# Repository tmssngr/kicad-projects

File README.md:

- [EEPROM flasher as Arduino shield](EPROM-Shield/README.md)

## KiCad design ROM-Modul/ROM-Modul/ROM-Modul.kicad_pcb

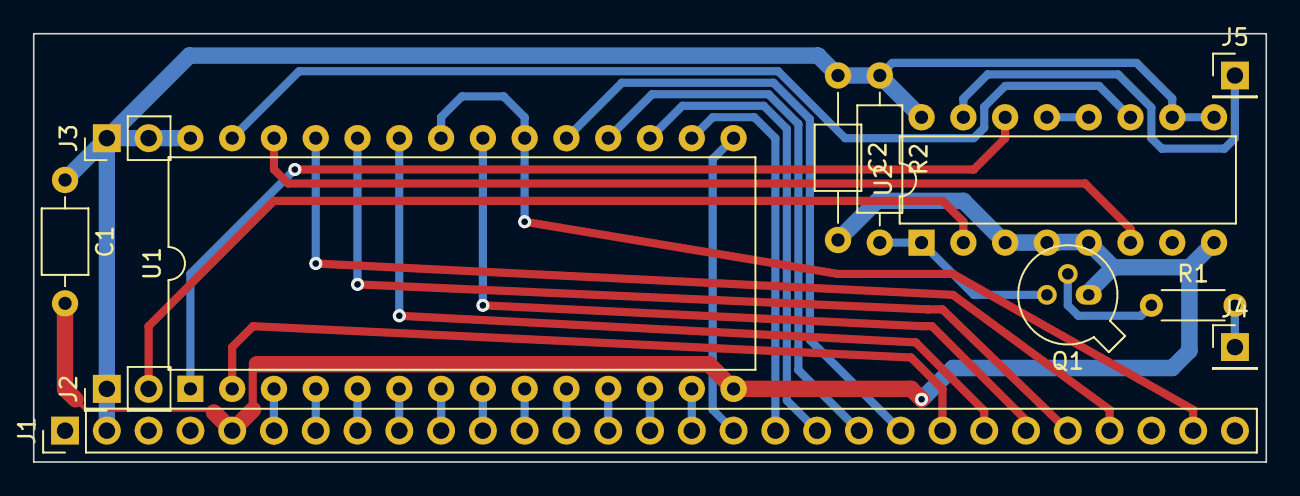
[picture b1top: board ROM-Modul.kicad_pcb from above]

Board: 2 copper layers, 74.9 x 26.0 mm, 12 parts (0 on the bottom side), 32 nets.

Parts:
C1: C; C_Axial_L3.8mm_D2.6mm_P7.50mm_Horizontal
C2: C; C_Axial_L3.8mm_D2.6mm_P10.00mm_Horizontal
J1: Conn_01x29; PinHeader_1x29_P2.54mm_Vertical
J2, J3: Conn_01x02; PinHeader_1x02_P2.54mm_Vertical
J4: /0; PinHeader_1x01_P2.54mm_Vertical
J5: Schritt; PinHeader_1x01_P2.54mm_Vertical
Q1: BC107; TO-18-3
R1: 1k; R_Axial_DIN0204_L3.6mm_D1.6mm_P5.08mm_Horizontal
R2: 10k; R_Axial_DIN0207_L6.3mm_D2.5mm_P10.16mm_Horizontal
U1: 27C512; DIP-28_W15.24mm
U2: 4029; DIP-16_W7.62mm

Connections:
/A0: J1.13, U1.10
/A1: J1.12, U1.9
/A2: J1.11, U1.8
/A3: J1.10, U1.7
/A4: J1.9, U1.6
/A5: J1.8, U1.5
/A6: J1.7, U1.4
/A7: J1.6, U1.3
/A8: J1.26, U1.25
/A9: J1.25, U1.24
/A10: J1.24, U1.21
/A11: J1.23, U1.23
/A12: J1.22, U1.2
/A13: U1.26, U2.6
/A14: U1.27, U2.11
/A15: U1.1, U2.14
/A16: J2.2, U2.2
/CS: J1.28, U1.20, U1.22
/D0: J1.14, U1.11
/D1: J1.15, U1.12
/D2: J1.16, U1.13
/D3: J1.17, U1.15
/D4: J1.18, U1.16
/D5: J1.19, U1.17
/D6: J1.20, U1.18
/D7: J1.21, U1.19
GND: C1.2, C2.2, J1.5, Q1.1, U1.14, U2.3, U2.4, U2.5, U2.8, U2.12, U2.13
unnamed: J4.1, R1.2
unnamed: J5.1, U2.15
unnamed: Q1.2, R1.1
unnamed: Q1.3, R2.2, U2.1
VCC: C1.1, C2.1, J1.2, J2.1, J3.1, J3.2, R2.1, U1.28, U2.9, U2.10, U2.16

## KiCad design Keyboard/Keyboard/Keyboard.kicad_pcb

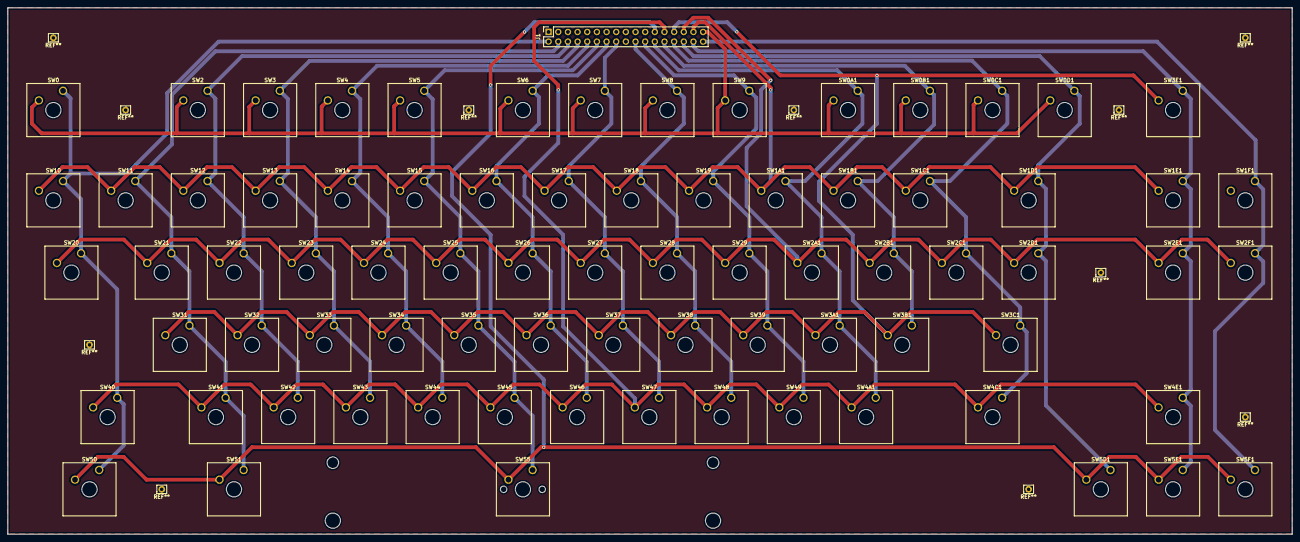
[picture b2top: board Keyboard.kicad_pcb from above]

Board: 2 copper layers, 337.8 x 138.4 mm, 78 parts (0 on the bottom side), 22 nets.

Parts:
J1: Conn_02x17_Odd_Even; PinSocket_2x17_P2.54mm_Vertical
SW0: Esc; SW_Cherry_MX_1.00u_Plate
SW0A1: F9; SW_Cherry_MX_1.00u_Plate
SW0B1: F10; SW_Cherry_MX_1.00u_Plate
SW0C1: F11; SW_Cherry_MX_1.00u_Plate
SW0D1: F12; SW_Cherry_MX_1.00u_Plate
SW1A1: 0; SW_Cherry_MX_1.00u_Plate
SW1B1: -; SW_Cherry_MX_1.00u_Plate
SW1C1: =; SW_Cherry_MX_1.00u_Plate
SW1D1: BS; SW_Cherry_MX_2.00u_Plate
SW1E1: Home; SW_Cherry_MX_1.00u_Plate
SW1F1: PageUp; SW_Cherry_MX_1.00u_Plate
SW2: F1; SW_Cherry_MX_1.00u_Plate
SW2A1: P; SW_Cherry_MX_1.00u_Plate
SW2B1: [; SW_Cherry_MX_1.00u_Plate
SW2C1: ]; SW_Cherry_MX_1.00u_Plate
SW2D1: \; SW_Cherry_MX_1.00u_Plate
SW2E1: End; SW_Cherry_MX_1.00u_Plate
SW2F1: PageDown; SW_Cherry_MX_1.00u_Plate
SW3: F2; SW_Cherry_MX_1.00u_Plate
SW3A1: ;; SW_Cherry_MX_1.00u_Plate
SW3B1: '; SW_Cherry_MX_1.00u_Plate
SW3C1: Enter; SW_Cherry_MX_2.00u_Plate
SW3E1: Del; SW_Cherry_MX_1.00u_Plate
SW4: F3; SW_Cherry_MX_1.00u_Plate
SW4A1: /; SW_Cherry_MX_1.00u_Plate
SW4C1: RShift; SW_Cherry_MX_2.00u_Plate
SW4E1: Up; SW_Cherry_MX_1.00u_Plate
SW5: F4; SW_Cherry_MX_1.00u_Plate
SW5D1: Left; SW_Cherry_MX_1.00u_Plate
SW5E1: Down; SW_Cherry_MX_1.00u_Plate
SW5F1: Right; SW_Cherry_MX_1.00u_Plate
SW6: F5; SW_Cherry_MX_1.00u_Plate
SW7: F6; SW_Cherry_MX_1.00u_Plate
SW8: F7; SW_Cherry_MX_1.00u_Plate
SW9: F8; SW_Cherry_MX_1.00u_Plate
SW10: Tilde; SW_Cherry_MX_1.00u_Plate
SW11: 1; SW_Cherry_MX_1.00u_Plate
SW12: 2; SW_Cherry_MX_1.00u_Plate
SW13: 3; SW_Cherry_MX_1.00u_Plate
SW14: 4; SW_Cherry_MX_1.00u_Plate
SW15: 5; SW_Cherry_MX_1.00u_Plate
SW16: 6; SW_Cherry_MX_1.00u_Plate
SW17: 7; SW_Cherry_MX_1.00u_Plate
SW18: 8; SW_Cherry_MX_1.00u_Plate
SW19: 9; SW_Cherry_MX_1.00u_Plate
SW20: Tab; SW_Cherry_MX_1.50u_Plate
SW21: Q; SW_Cherry_MX_1.00u_Plate
SW22: W; SW_Cherry_MX_1.00u_Plate
SW23: E; SW_Cherry_MX_1.00u_Plate
SW24: R; SW_Cherry_MX_1.00u_Plate
SW25: T; SW_Cherry_MX_1.00u_Plate
SW26: Y; SW_Cherry_MX_1.00u_Plate
SW27: U; SW_Cherry_MX_1.00u_Plate
SW28: I; SW_Cherry_MX_1.00u_Plate
SW29: O; SW_Cherry_MX_1.00u_Plate
SW31: A; SW_Cherry_MX_1.00u_Plate
SW32: S; SW_Cherry_MX_1.00u_Plate
SW33: D; SW_Cherry_MX_1.00u_Plate
SW34: F; SW_Cherry_MX_1.00u_Plate
SW35: G; SW_Cherry_MX_1.00u_Plate
SW36: H; SW_Cherry_MX_1.00u_Plate
SW37: J; SW_Cherry_MX_1.00u_Plate
SW38: K; SW_Cherry_MX_1.00u_Plate
SW39: L; SW_Cherry_MX_1.00u_Plate
SW40: Shift; SW_Cherry_MX_2.00u_Plate
SW41: Z; SW_Cherry_MX_1.00u_Plate
SW42: X; SW_Cherry_MX_1.00u_Plate
SW43: C; SW_Cherry_MX_1.00u_Plate
SW44: V; SW_Cherry_MX_1.00u_Plate
SW45: B; SW_Cherry_MX_1.00u_Plate
SW46: N; SW_Cherry_MX_1.00u_Plate
SW47: M; SW_Cherry_MX_1.00u_Plate
SW48: ,; SW_Cherry_MX_1.00u_Plate
SW49: .; SW_Cherry_MX_1.00u_Plate
SW50: Ctrl; SW_Cherry_MX_1.25u_Plate
SW51: Alt; SW_Cherry_MX_1.25u_Plate
SW55: Space; SW_Cherry_MX_6.25u_PCB

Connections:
unnamed: J1.2, SW0.1, SW10.1, SW20.1, SW40.1, SW50.1
unnamed: J1.4, SW11.1, SW21.1, SW31.1, SW41.1, SW51.1
unnamed: J1.6, SW2.1, SW12.1, SW22.1, SW32.1, SW42.1
unnamed: J1.8, SW3.1, SW13.1, SW23.1, SW33.1, SW43.1
unnamed: J1.10, SW4.1, SW14.1, SW24.1, SW34.1, SW44.1
unnamed: J1.12, SW5.1, SW15.1, SW25.1, SW35.1, SW45.1, SW55.1
unnamed: J1.14, SW6.1, SW16.1, SW26.1, SW36.1, SW46.1
unnamed: J1.16, SW7.1, SW17.1, SW27.1, SW37.1, SW47.1
unnamed: J1.20, SW8.1, SW18.1, SW28.1, SW38.1, SW48.1
unnamed: J1.22, SW9.1, SW19.1, SW29.1, SW39.1, SW49.1
unnamed: J1.23, SW5D1.2, SW5E1.2, SW5F1.2, SW50.2, SW51.2, SW55.2
unnamed: J1.24, SW0A1.1, SW1A1.1, SW2A1.1, SW3A1.1, SW4A1.1
unnamed: J1.25, SW4A1.2, SW4C1.2, SW4E1.2, SW40.2, SW41.2, SW42.2, SW43.2, SW44.2, SW45.2, SW46.2, SW47.2, SW48.2, SW49.2
unnamed: J1.26, SW0B1.1, SW1B1.1, SW2B1.1, SW3B1.1
unnamed: J1.27, SW3A1.2, SW3B1.2, SW3C1.2, SW3E1.2, SW31.2, SW32.2, SW33.2, SW34.2, SW35.2, SW36.2, SW37.2, SW38.2, SW39.2
unnamed: J1.28, SW0C1.1, SW1C1.1, SW2C1.1, SW3C1.1, SW4C1.1
unnamed: J1.29, SW2A1.2, SW2B1.2, SW2C1.2, SW2D1.2, SW2E1.2, SW2F1.2, SW20.2, SW21.2, SW22.2, SW23.2, SW24.2, SW25.2, SW26.2, SW27.2, SW28.2, SW29.2
unnamed: J1.30, SW0D1.1, SW1D1.1, SW2D1.1, SW5D1.1
unnamed: J1.31, SW1A1.2, SW1B1.2, SW1C1.2, SW1D1.2, SW1E1.2, SW1F1.2, SW10.2, SW11.2, SW12.2, SW13.2, SW14.2, SW15.2, SW16.2, SW17.2, SW18.2, SW19.2
unnamed: J1.32, SW1E1.1, SW2E1.1, SW3E1.1, SW4E1.1, SW5E1.1
unnamed: J1.33, SW0.2, SW0A1.2, SW0B1.2, SW0C1.2, SW0D1.2, SW2.2, SW3.2, SW4.2, SW5.2, SW6.2, SW7.2, SW8.2, SW9.2
unnamed: J1.34, SW1F1.1, SW2F1.1, SW5F1.1

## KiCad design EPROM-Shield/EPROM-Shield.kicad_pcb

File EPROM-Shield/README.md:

# EEPROMmer as Arduino Shield
This is my first attempt to create a EEPROMmer in the form of an Arduino shield.

## Alternative Approaches:
- Arduino-Mega-based: https://github.com/bmpc/arduino_eeprom_programmer
- Very good explanation of steps from breadboard: https://www.youtube.com/watch?v=K88pgWhEb1M

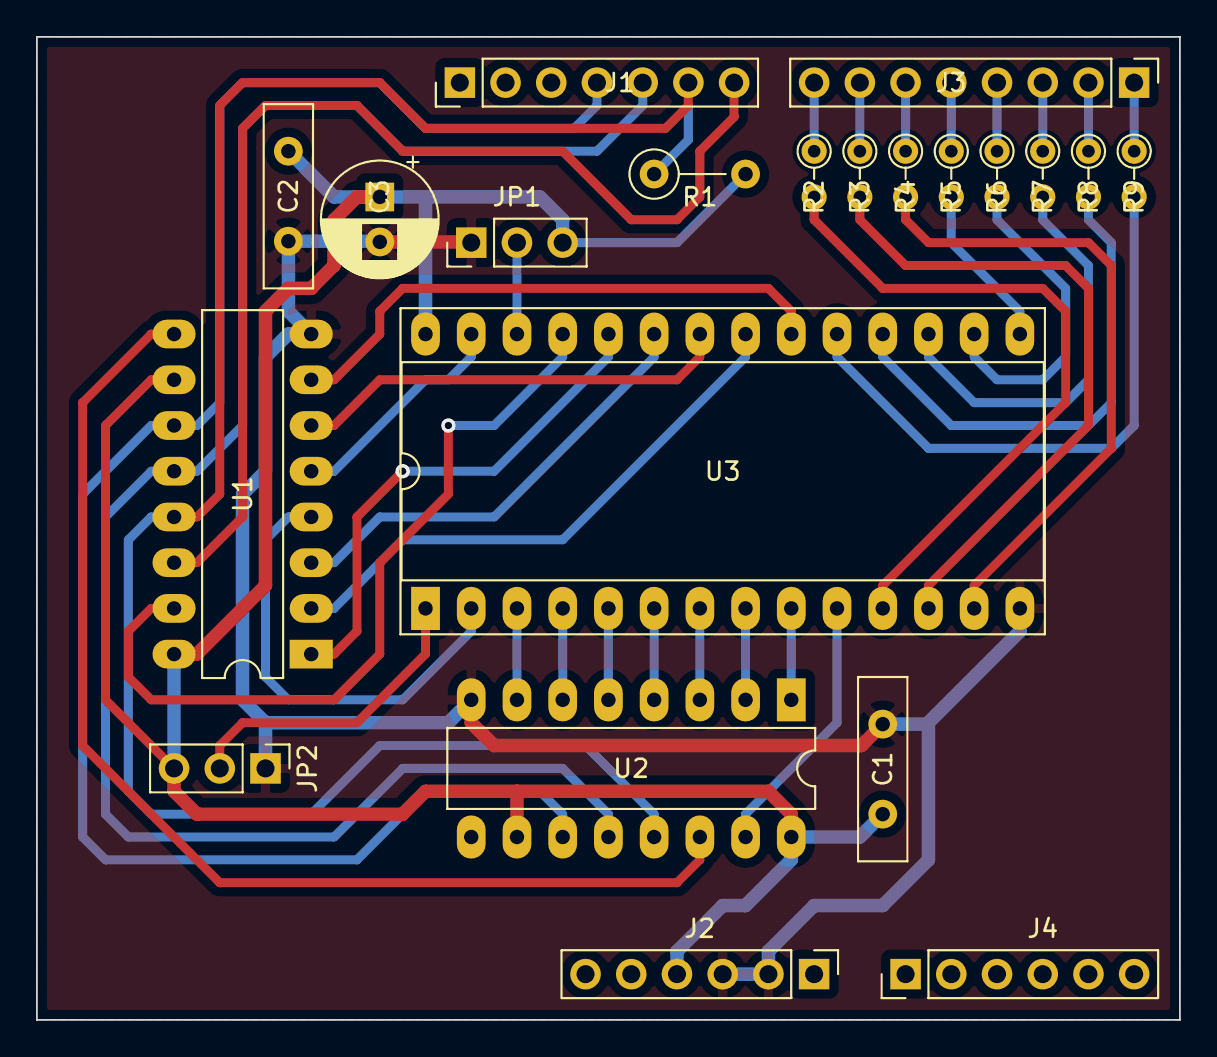
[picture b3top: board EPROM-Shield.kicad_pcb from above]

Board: 2 copper layers, 63.5 x 54.6 mm, 21 parts (0 on the bottom side), 41 nets.

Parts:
C1, C2: 100n; C_Disc_D10.0mm_W2.5mm_P5.00mm
C3: 47u; CP_Radial_D6.3mm_P2.50mm
J1: Conn_01x07; PinHeader_1x07_P2.54mm_Vertical
J2, J4: Conn_01x06; PinHeader_1x06_P2.54mm_Vertical
J3: Conn_01x08; PinHeader_1x08_P2.54mm_Vertical
JP1: A13 1-0; PinHeader_1x03_P2.54mm_Vertical
JP2: A14 1-0; PinHeader_1x03_P2.54mm_Vertical
R1: 10k; R_Axial_DIN0207_L6.3mm_D2.5mm_P5.08mm_Vertical
R2, R3, R4, R5, R6, R7, R8, R9: 510; R_Axial_DIN0204_L3.6mm_D1.6mm_P2.54mm_Vertical
U1, U2: 74LS595; DIP-16_W7.62mm_LongPads
U3: 28C256; DIP-28_W15.24mm_Socket_LongPads

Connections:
/A0: U2.15, U3.10
/A1: U2.1, U3.9
/A2: U2.2, U3.8
/A3: U2.3, U3.7
/A4: U2.4, U3.6
/A5: U2.5, U3.5
/A6: U2.6, U3.4
/A7: U2.7, U3.3
/A8: U1.15, U3.25
/A9: U1.1, U3.24
/A10: U1.2, U3.21
/A11: U1.3, U3.23
/A12: U1.4, U3.2
/A13: JP1.2, U3.26
/A14: JP2.2, U3.1
/CS: U1.7, U3.20
/D0: J3.8, R2.1
/D1: J3.7, R3.1
/D2: J3.6, R4.1
/D3: J3.5, R5.1
/D4: J3.4, R6.1
/D5: J3.3, R7.1
/D6: J3.2, R8.1
/D7: J3.1, R9.1
/OE: U1.6, U3.22
/WE: U1.5, U3.27
GND: C1.2, C2.2, C3.2, J2.2, J2.3, JP1.1, JP2.1, U1.8, U2.8, U3.14
unnamed: J1.4, U1.11, U2.11
unnamed: J1.5, U1.12, U2.12
unnamed: J1.6, R1.1, U1.13, U2.13
unnamed: J1.7, U1.14
unnamed: R2.2, U3.11
unnamed: R3.2, U3.12
unnamed: R4.2, U3.13
unnamed: R5.2, U3.15
unnamed: R6.2, U3.16
unnamed: R7.2, U3.17
unnamed: R8.2, U3.18
unnamed: R9.2, U3.19
unnamed: U1.9, U2.14
VCC: C1.1, C2.1, C3.1, J2.4, JP1.3, JP2.3, R1.2, U1.10, U1.16, U2.10, U2.16, U3.28

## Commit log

2022-05-13 EPROM-Shield: add GND fill zones
2022-05-13 EPROM-Shield: first attempt
2022-05-13 .gitignore
2022-05-13 EPROM-Shield: gerber files
2022-05-13 change GND/VSS line width to 1mm
2022-05-13 EPROM-Shield: several fixes - more clear schematic with regards to the shift register control pins - fix the D0-D7 connections, resulting in smaller board - fix R values and positions
2022-05-13 EPROM-Shield.pdf
2022-05-13 add README.md
2022-05-14 EPROM-Shield
    - D0/D1 can optionally be connected to AD0/AD1 (because D0/D1 are used for serial port on some Arduino boards)
    - connected GND on D8-D13 connector
    - fix C3 footprint
2022-05-14 Keyboard.pdf
2022-05-14 Keyboard with Cherry MX
2022-05-14 Keyboard: gerber
2022-06-16 ROM-Modul
2022-06-16 The Arduino EEPROMer-shield has been relocated to https://github.com/tmssngr/arduino-eeprommer
